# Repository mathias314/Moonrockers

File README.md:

# About | Moonrockers - Robotic Mining Challenge

Programming a robot to compete autonomously (as much as possible) in the robotic mining challenge.

Please see more in-depth documentation in the System Document in the "about" project.

A high level overview of each of the folders in this project follows:

docker - The docker folder contains the content for the control station and robot docker container. Run the build.sh and run.sh script in order to launch the driver station and robot instances.

kinectPlaying - Contains scripts for running the obstacle detection script, using the Azure Kinect DK.

pd-board - Legacy files from the design of the power distribution from the 2021-2022 team.

ros - Code for all of the ROS nodes in the system. Includes both the control station docker containers and the robot docker containers. See the system doc for more detailed information and further information on how to build and use.

tags - Example AruCo tags.

uc - Contains code for the microcontrollers on the robot. Includes code for Woody and the final robot.

## Team
- Justin Kemp
- Kaden Adrian
- Mathew Clutter

## Technical Advisor
- Samuel Ryckman (Samuel.Ryckman@mines.sdsmt.edu)

# Faculty Advisors
- Brian Butterfield (brian.butterfield@sdsmt.edu)
- Jason Ash (jason.ash@sdsmt.edu)
- Lowell Kolb (lowell.kolb@sdsmt.edu)

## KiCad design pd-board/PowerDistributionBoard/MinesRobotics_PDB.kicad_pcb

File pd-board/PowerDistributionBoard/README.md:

# power-distribution-board
kicad files for a power distribution board

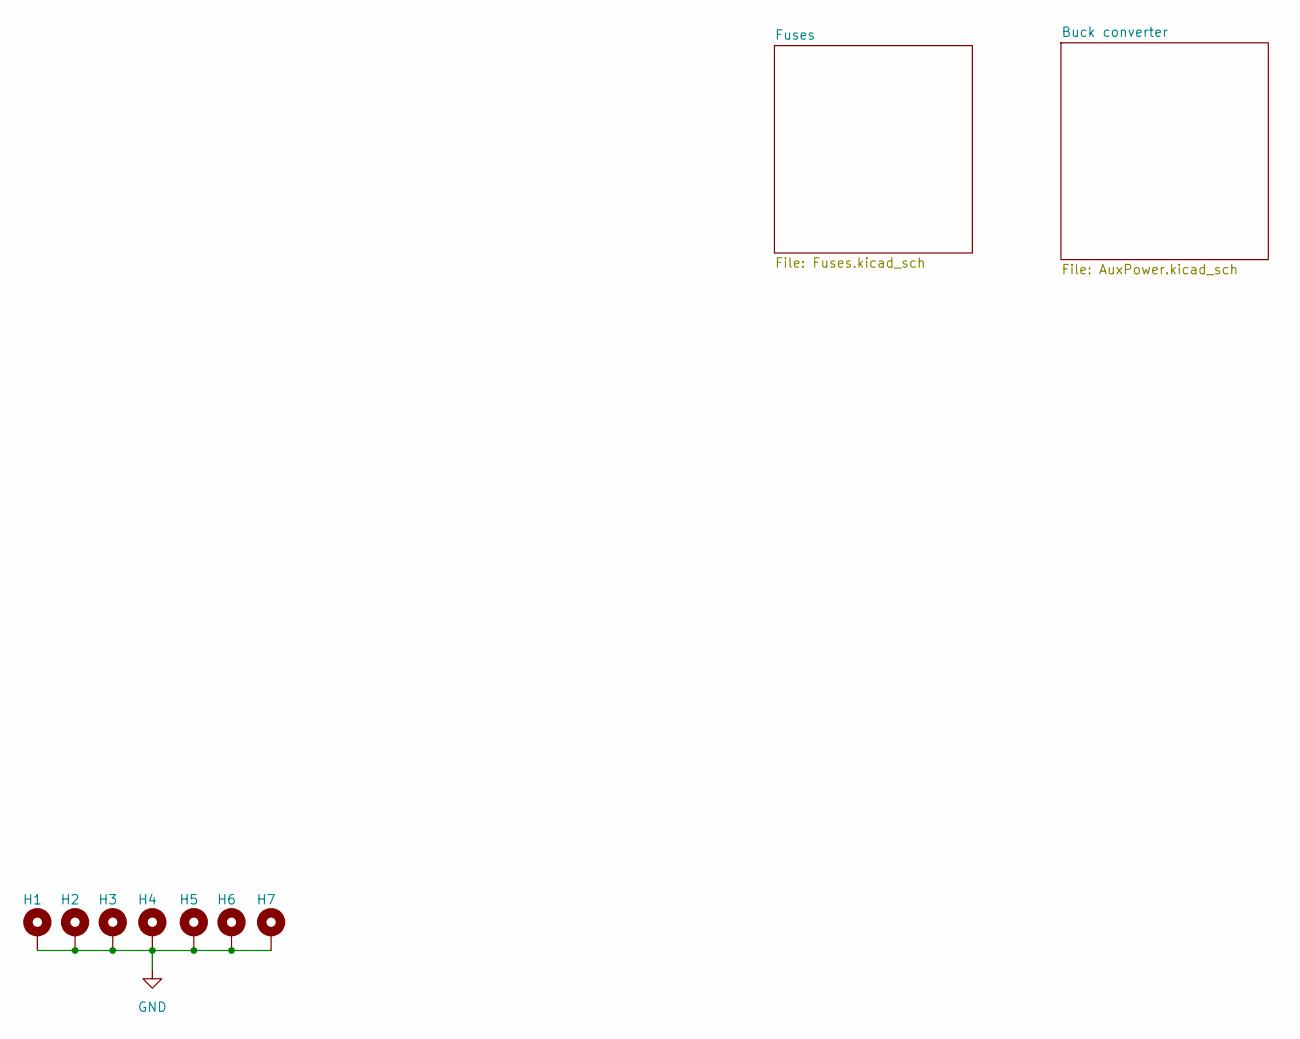
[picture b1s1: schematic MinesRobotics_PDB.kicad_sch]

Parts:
H1, H2, H3, H4, H5, H6, H7: MountingHole_Pad; MountingHole_3.2mm_M3_DIN965_Pad

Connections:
GND: H1.1, H2.1, H3.1, H4.1, H5.1, H6.1, H7.1; also elsewhere on the board

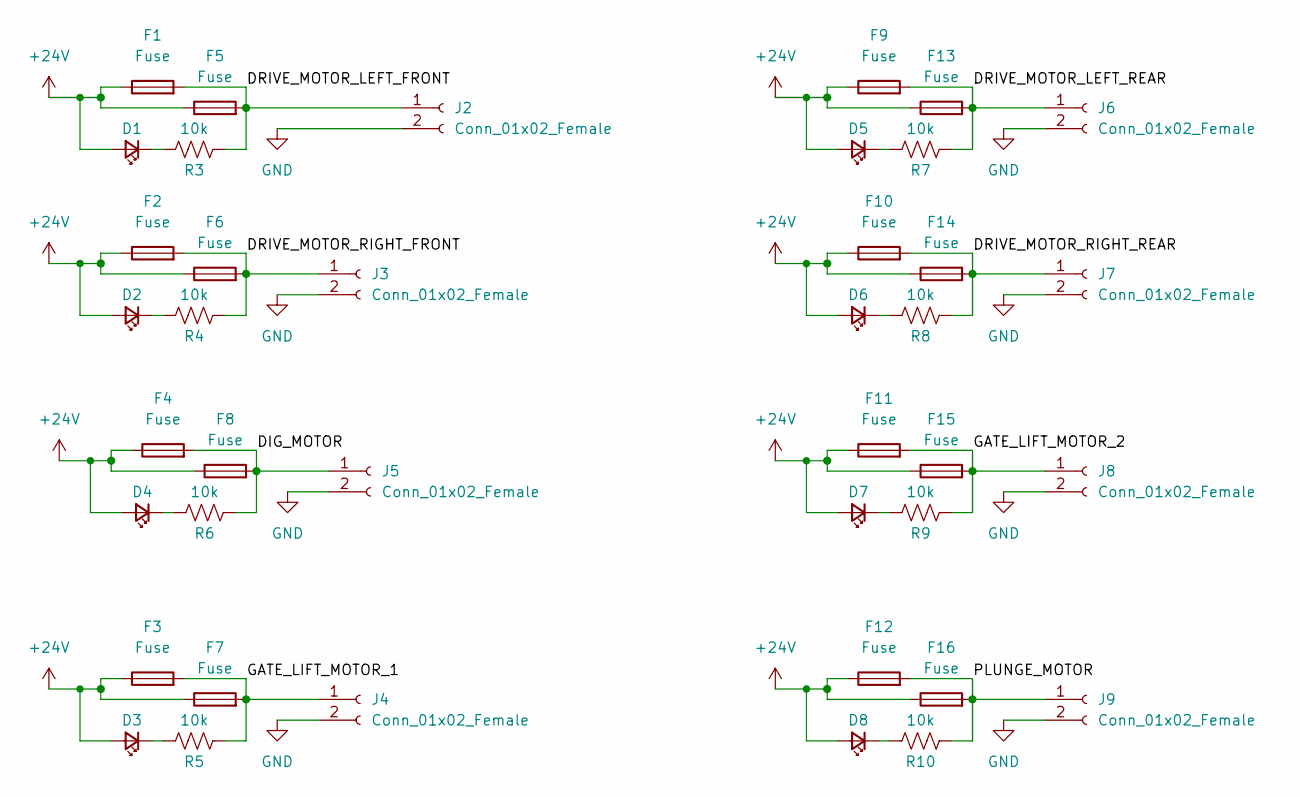
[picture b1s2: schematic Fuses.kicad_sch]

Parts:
D1, D2, D3, D4, D5, D6, D7, D8: LED_Small; LED_0805_2012Metric
F1, F2, F3, F4, F5, F6, F7, F8, F9, F10, F11, F12, F13, F14, F15, F16: Fuse; Fuseholder_Blade_Mini_Keystone_3568
J2, J3, J4, J5, J6, J7, J8, J9: Conn_01x02_Female; PowerPole_45A_Vert
R3, R4, R5, R6, R7, R8, R9, R10: 10k; R_0805_2012Metric

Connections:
+24V: D1.2 (A), D2.2 (A), D3.2 (A), D4.2 (A), D5.2 (A), D6.2 (A), D7.2 (A), D8.2 (A), F1.1, F2.1, F3.1, F4.1, F5.1, F6.1, F7.1, F8.1, F9.1, F10.1, F11.1, F12.1, F13.1, F14.1, F15.1, F16.1; also elsewhere on the board
/Fuses/DIG_MOTOR: F4.2, F8.2, J5.1, R6.2
/Fuses/DRIVE_MOTOR_LEFT_FRONT: F1.2, F5.2, J2.1, R3.2
/Fuses/DRIVE_MOTOR_LEFT_REAR: F9.2, F13.2, J6.1, R7.2
/Fuses/DRIVE_MOTOR_RIGHT_FRONT: F2.2, F6.2, J3.1, R4.2
/Fuses/DRIVE_MOTOR_RIGHT_REAR: F10.2, F14.2, J7.1, R8.2
/Fuses/GATE_LIFT_MOTOR_1: F3.2, F7.2, J4.1, R5.2
/Fuses/GATE_LIFT_MOTOR_2: F11.2, F15.2, J8.1, R9.2
/Fuses/PLUNGE_MOTOR: F12.2, F16.2, J9.1, R10.2
GND: J2.2, J3.2, J4.2, J5.2, J6.2, J7.2, J8.2, J9.2; also elsewhere on the board
unnamed: D1.1 (K), R3.1
unnamed: D2.1 (K), R4.1
unnamed: D3.1 (K), R5.1
unnamed: D4.1 (K), R6.1
unnamed: D5.1 (K), R7.1
unnamed: D6.1 (K), R8.1
unnamed: D7.1 (K), R9.1
unnamed: D8.1 (K), R10.1

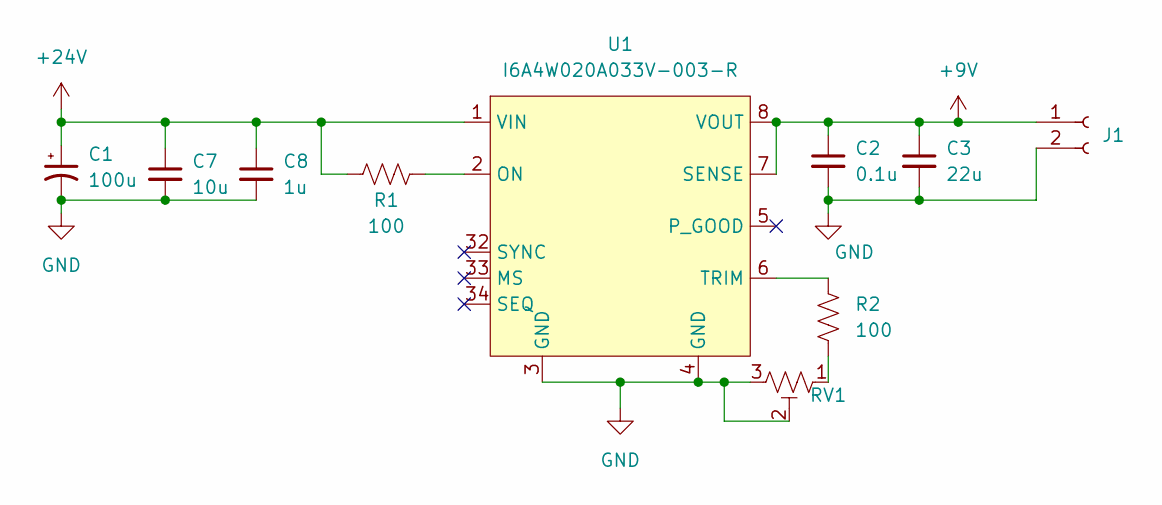
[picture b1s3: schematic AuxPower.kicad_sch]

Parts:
C1: 100u; CP_Elec_10x10
C2: 0.1u; C_0603_1608Metric
C3: 22u; CP_EIA-7343-15_Kemet-W
C7: 10u; C_0603_1608Metric
C8: 1u; C_0603_1608Metric
J1: Conn_01x02_Female; JST_XH_B2B-XH-A_1x02_P2.50mm_Vertical
R1, R2: 100; R_0805_2012Metric
RV1: 50k; Potentiometer_Bourns_3266Y_Vertical
U1: I6A4W020A033V-003-R; i6A4W

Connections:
+9V: C2.1, C3.1, J1.1, U1.7 (SENSE), U1.8 (VOUT)
+24V: C1.1, C7.1, C8.1, R1.1, U1.1 (VIN); also elsewhere on the board
GND: C1.2, C2.2, C3.2, C7.2, C8.2, J1.2, RV1.2, RV1.3, U1.3 (GND), U1.4 (GND); also elsewhere on the board
unnamed: R1.2, U1.2 (ON)
unnamed: R2.1, U1.6 (TRIM)
unnamed: R2.2, RV1.1

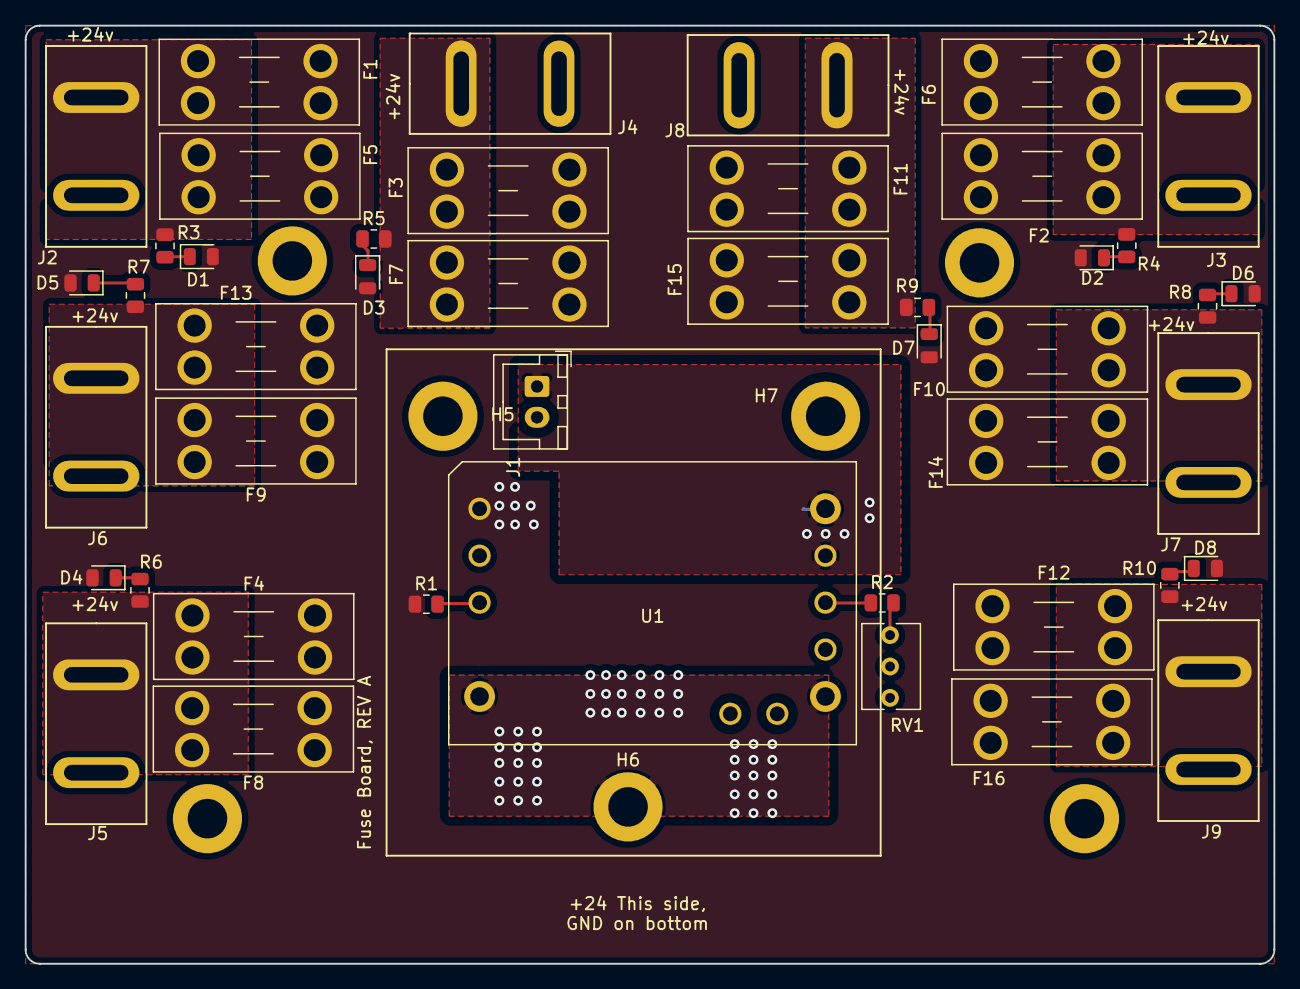
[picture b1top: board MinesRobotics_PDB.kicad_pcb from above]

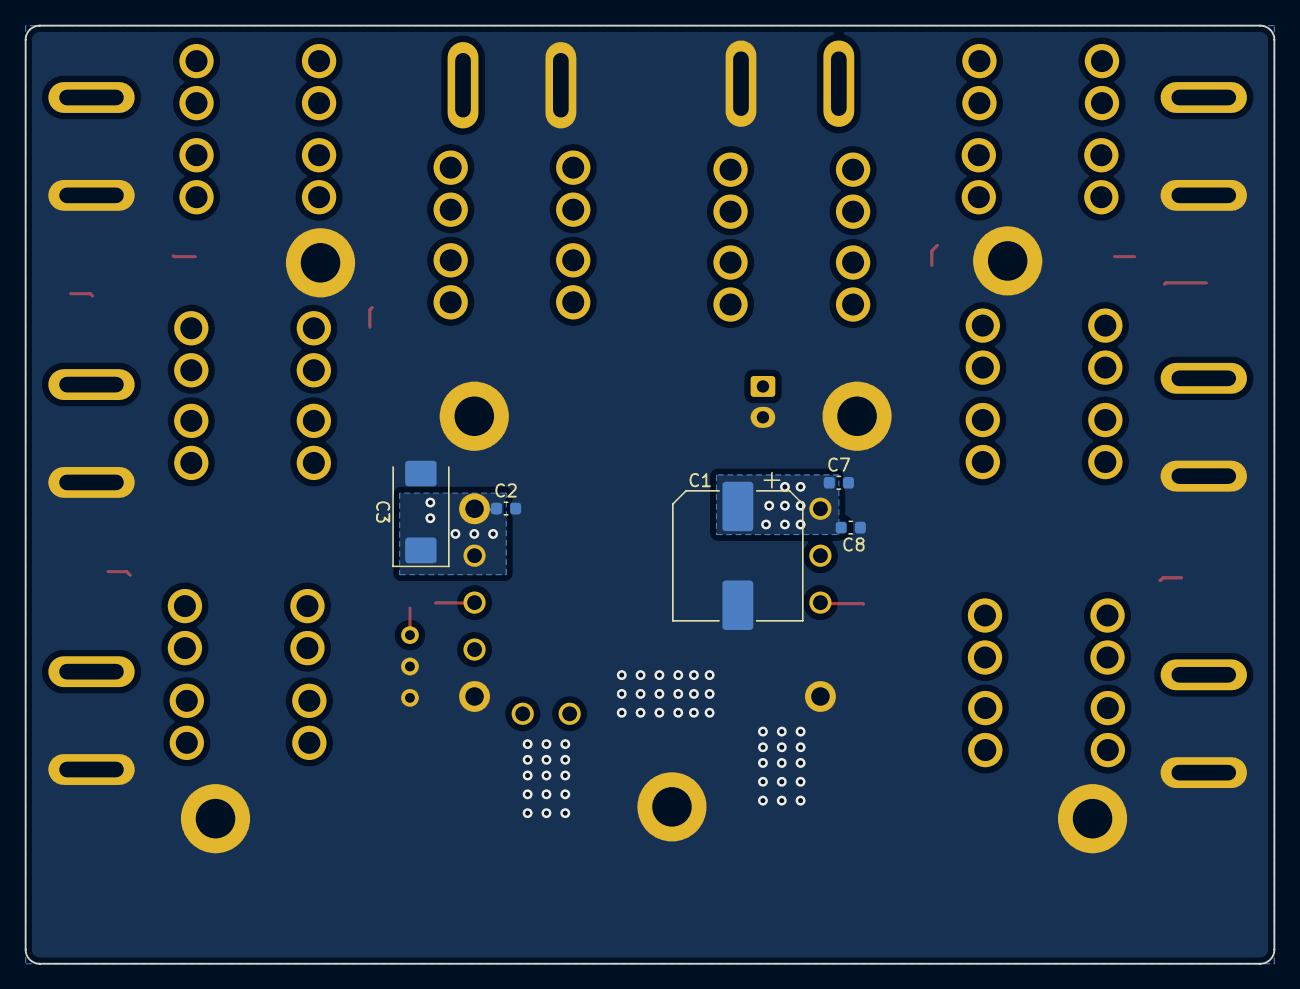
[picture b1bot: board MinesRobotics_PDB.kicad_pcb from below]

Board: 2 copper layers, 101.1 x 75.9 mm, 57 parts (5 on the bottom side), 22 nets.

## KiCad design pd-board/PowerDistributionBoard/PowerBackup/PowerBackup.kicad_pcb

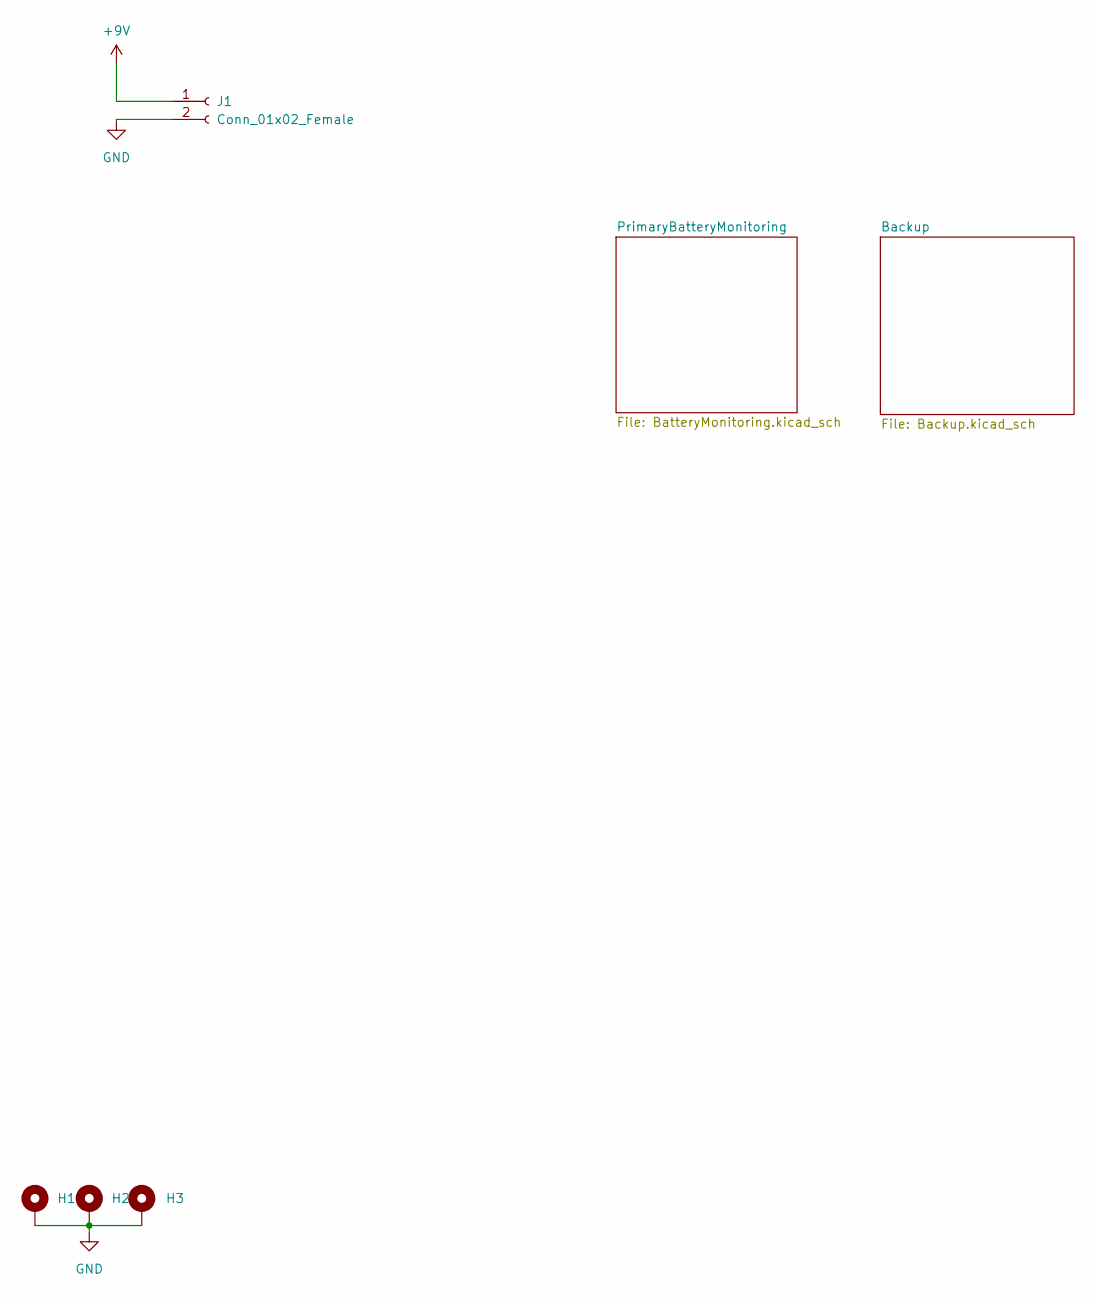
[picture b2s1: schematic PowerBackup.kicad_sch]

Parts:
H1, H2, H3: MountingHole_Pad; MountingHole_2.7mm_M2.5_Pad
J1: Conn_01x02_Female; JST_XH_B2B-XH-A_1x02_P2.50mm_Vertical

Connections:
+9V: J1.1; also elsewhere on the board
GND: H1.1, H2.1, H3.1, J1.2; also elsewhere on the board

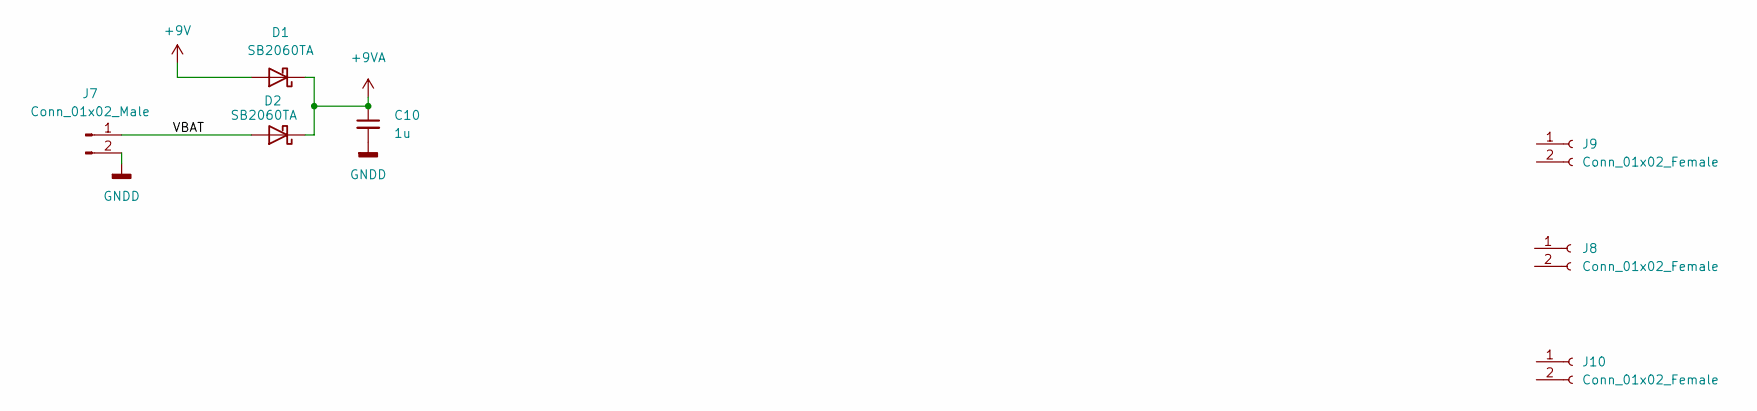
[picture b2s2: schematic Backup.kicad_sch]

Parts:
C10: 1u; C_0805_2012Metric
D1, D2: SB2060TA; D_A-405_P5.08mm_Vertical_KathodeUp
J7: Conn_01x02_Male; JST_XH_B2B-XH-A_1x02_P2.50mm_Vertical
J8, J9, J10: Conn_01x02_Female; JST_XH_B2B-XH-A_1x02_P2.50mm_Vertical

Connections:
+9V: D1.2 (A); also elsewhere on the board
+9VA: C10.1, D1.1 (K), D2.1 (K)
/Backup/VBAT: D2.2 (A), J7.1
GNDD: C10.2, J7.2

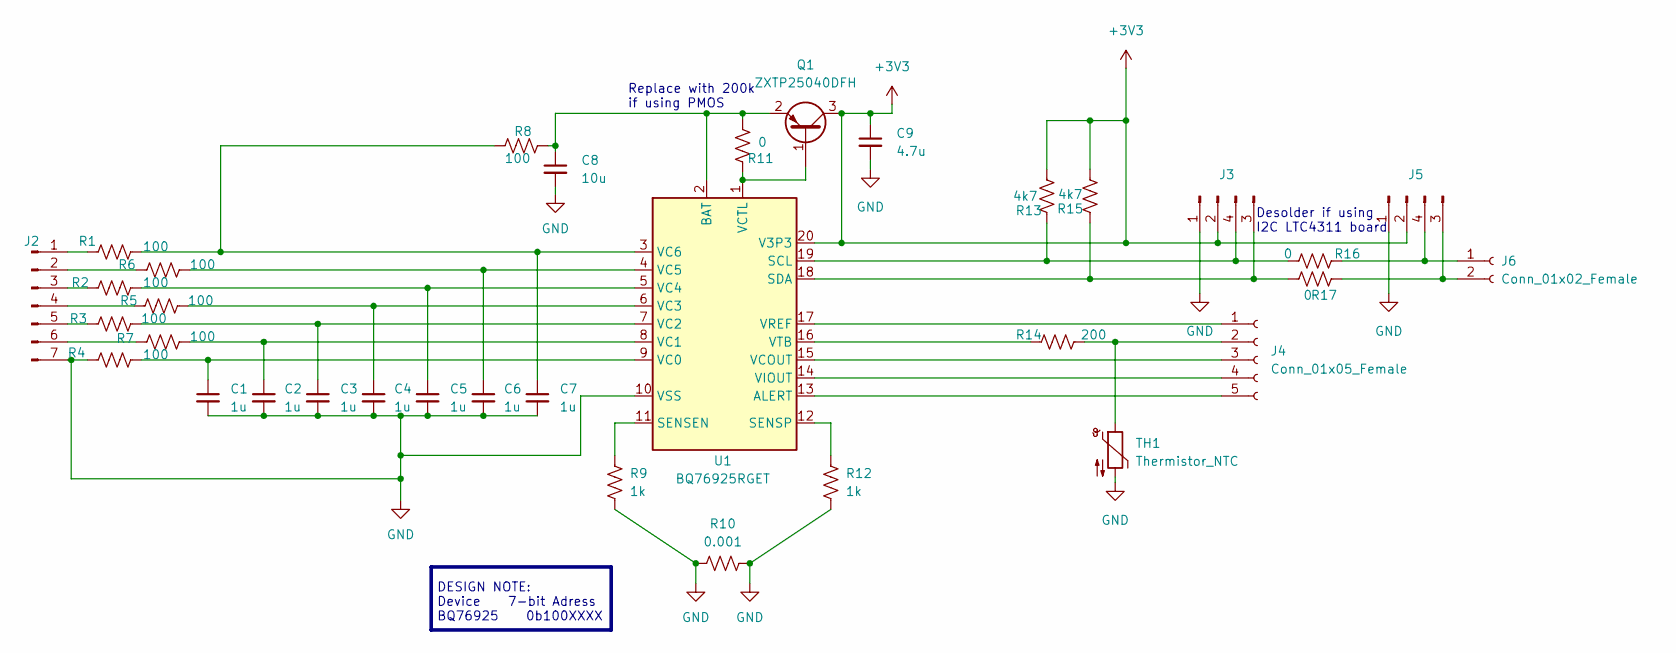
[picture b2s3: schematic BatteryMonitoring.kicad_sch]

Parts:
C1, C2, C3, C4, C5, C6, C7: 1u; C_0805_2012Metric
C8: 10u; C_0805_2012Metric
C9: 4.7u; C_0805_2012Metric
J2: Conn_01x07_Male; JST_XH_B7B-XH-A_1x07_P2.50mm_Vertical
J3, J5: Conn_01x04_Male
J4: Conn_01x05_Female; PinHeader_1x05_P1.00mm_Vertical_SMD_Pin1Left
J6: Conn_01x02_Female; JST_XH_B2B-XH-A_1x02_P2.50mm_Vertical
Q1: ZXTP25040DFH; SOT-23
R1, R2, R3, R4, R5, R6, R7, R8: 100; R_0805_2012Metric
R9, R12: 1k; R_0805_2012Metric
R10: 0.001; R_0805_2012Metric; MFG# CSRL3-0R001F8
R11, R16, R17: 0; R_0805_2012Metric
R13, R15: 4k7; R_0805_2012Metric
R14: 200; R_0805_2012Metric
TH1: Thermistor_NTC; R_0805_2012Metric
U1: BQ76925RGET; HVQFN-24-1EP_4x4mm_P0.5mm_EP2.5x2.5mm

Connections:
+3V3: C9.1, J3.2, J5.2, Q1.3 (C), R13.2, R15.2, U1.20 (V3P3)
GND: C1.2, C2.2, C3.2, C4.2, C5.2, C6.2, C7.2, C8.2, C9.2, J2.7, J3.1, J5.1, R4.1, R9.2, R10.1, R10.2, R12.2, TH1.2, U1.10 (VSS); also elsewhere on the board
unnamed: C1.1, R4.2, U1.9 (VC0)
unnamed: C2.1, R7.2, U1.8 (VC1)
unnamed: C3.1, R3.2, U1.7 (VC2)
unnamed: C4.1, R5.2, U1.6 (VC3)
unnamed: C5.1, R2.2, U1.5 (VC4)
unnamed: C6.1, R6.2, U1.4 (VC5)
unnamed: C7.1, R1.2, R8.1, U1.3 (VC6)
unnamed: C8.1, Q1.2 (E), R8.2, R11.2, U1.2 (BAT)
unnamed: J2.1, R1.1
unnamed: J2.2, R6.1
unnamed: J2.3, R2.1
unnamed: J2.4, R5.1
unnamed: J2.5, R3.1
unnamed: J2.6, R7.1
unnamed: J3.3 (Pin_4), R15.1, R17.2, U1.18 (SDA)
unnamed: J3.4 (Pin_3), R13.1, R16.2, U1.19 (SCL)
unnamed: J4.1, U1.17 (VREF)
unnamed: J4.2, R14.2, TH1.1
unnamed: J4.3, U1.15 (VCOUT)
unnamed: J4.4, U1.14 (VIOUT)
unnamed: J4.5, U1.13 (ALERT)
unnamed: J5.3 (Pin_4), J6.2, R17.1
unnamed: J5.4 (Pin_3), J6.1, R16.1
unnamed: Q1.1 (B), R11.1, U1.1 (VCTL)
unnamed: R9.1, U1.11 (SENSEN)
unnamed: R12.1, U1.12 (SENSP)
unnamed: R14.1, U1.16 (VTB)

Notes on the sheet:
Desolder if using I2C LTC4311 board
Replace with 200k if using PMOS
DESIGN NOTE: Device 7-bit Adress BQ76925 0b100XXXX

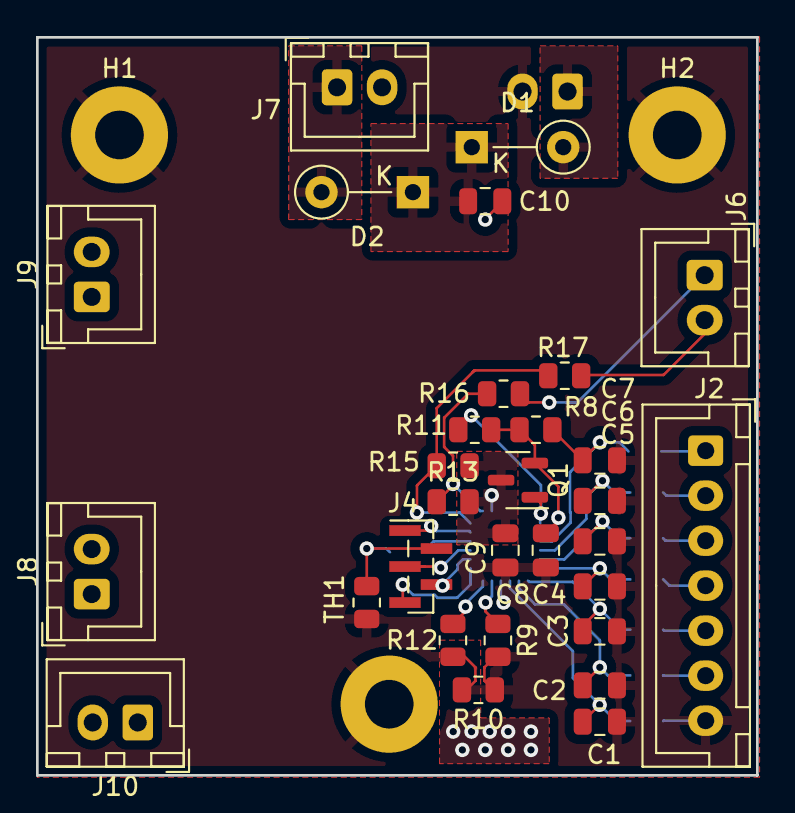
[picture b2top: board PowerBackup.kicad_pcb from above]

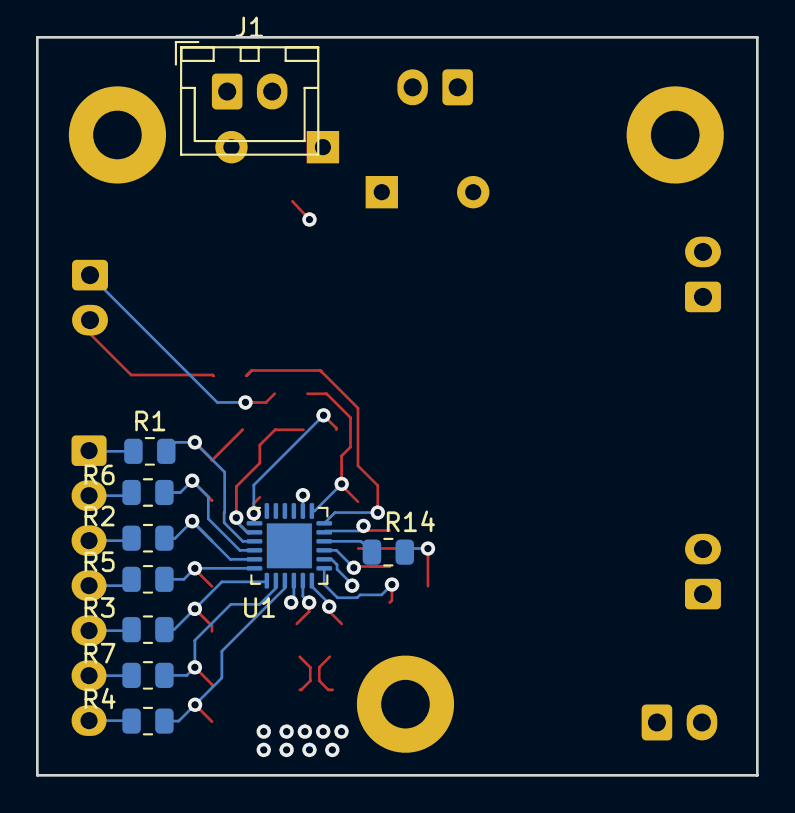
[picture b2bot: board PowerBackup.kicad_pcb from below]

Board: 4 copper layers, 40.0 x 41.0 mm, 43 parts (10 on the bottom side), 33 nets.

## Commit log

2022-11-02 Initing a readme
2022-11-02 Resolve "Adding last year's production code"
2022-12-05 Fix issues from Arduino lib updates over summer (#22)
    Updates over the summer to the CAN lib we are using and also some problems with compatibility of the custom PWM lib we wrote for the Nano 33 IOT when used with other boards was making things break. T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
2022-12-05 Implement basic CTRE MC functionality (#28)
    Moved common code from Spark MAX class to a common base class (FrcMotorController). All motor controllers will inherit from this. Basic control is working, but strange oddity to note: the CTRE motor 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
2022-12-06 Mostly implemented test chassis code and did some cleanup (https://gitlab.com/sdmines/projects/moonrockers/2022/controls/-/issues/31)
2022-12-07 Finish code for test chassis (https://gitlab.com/sdmines/projects/moonrockers/2022/controls/-/issues/31)
2022-12-09 Resolve "Drive robot from point to hopper using Aruco tag"
2022-12-27 Add code for interfacing with cheapo motors (#37)
    Code for controlling the motor and reading from the tachometer works. Need to add logic for determining direction. Also tuned the tachometer filter (mostly). Looks like we *should* be able to use the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
2023-01-10 Add some testing PID code (#36)
2023-01-14 Resolve "Check if OpenCV versions are compatible between the Kinect and Aruco"
2023-01-17 Increase PID velocity limits to 230 rmp
2023-01-17 Resolve "Unhardcode Absolute Path to Camera Calibration"
2023-01-17 Add more testing control options for PWM motor (#41)
2023-01-17 Consider direction in encoder's estimate (#41)
    The encoder class's estimateSpeed function was not considering direction in
    it's RPM calculation, resulting in it always reporting a positive
    value. An overloaded version of the function was added to consider the
    sign of the target speed in order to properly report the sign of the
    motor velocity.
    The motor controller seems to have an issue where its speed will not
2023-01-19 Resolve "Add Orientation data to Poser Output"
2023-01-20 Resolve "Average out Aruco Readings"
2023-01-24 Use sign of motor power to inform motor direction
2023-02-15 Use multiple static instances of Encoder class #49
2023-02-16 Fix uc proj structure issues and split out FRC motor lib
    - Moved some source files from the lib/main folder into the include and src folders. This will make it easier to exclude/include files when building examples.
    - Split out the FRC motor controllers library into a seperate repo. This is being developed by multiple groups simultaneously who are using it, so having this in a single repo where all groups may us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
2023-02-16 Add missing changes from prev commit to config file
2023-02-25 Add the Arduino Due configuration to project (#55)
2023-02-25 Fix encoder class (#56)
2023-03-02 Add support for Adafruit Metro M4 #57
2023-03-03 ported robot code to Docker, everything builds as it should
2023-03-03 Adding tracking for smaller tags
2023-03-04 Resolve "Update Production Readme"
2023-03-07 added YouCompleteMe ROS integration to the robot Docker container
2023-03-21 Fixing some incorrect pinouts
2023-03-28 Finalized wiring
2023-03-30 Started on new driver class
2023-03-31 Resolve "Fix Control Station Docker Container"
2023-04-05 Workday 4-4-2023
2023-04-05 Workday 4-4-2023 part 2
2023-04-05 Workday 4-4-2023 part 3
2023-04-06 Workday 4-6-2023
2023-04-07 Resolve "Implement obstacle identification with Kinect data"
2023-04-11 Workday 4-10-2023
2023-04-11 Steer PID mostly working
2023-04-12 Checkpoint 2240 4-11-2023
2023-04-12 Resolve "Slow autoDrive update speed"
2023-04-13 Resolve "Automate ROS launching for robot and control station"
2023-04-13 Design fair bare minimum
2023-04-13 Resolve "Add rosserial to robot docker"
2023-04-13 Resolve "Get Kinect Working within the ROS Setup on the Bot"
2023-04-13 Steering PID tuned
2023-04-13 Woody keyboard control in SAM_test.cpp
2023-04-18 Post design-fair
2023-04-27 Getting Woody Following an Aruco Tag
2023-04-28 Resolve "Rename sticks to driveStick and steerStick"
2023-04-28 Resolve "Update READMES"
2023-04-30 Resolve "Change subscribers in Woody microcontroller code"
